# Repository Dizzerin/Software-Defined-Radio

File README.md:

# Software-Defined-Radio
This project is a quadrature sampling down converter software defined radio reciver for Engineering Electronics II at Walla Walla University.
My partners for this project were [Darius Felder](https://github.com/darius3241) and [Eric Walsh](https://github.com/Eric-Walsh).
For a quick look at the final results of our project jump to [results](#results).
For a quick setup guide jump to [Quisk setup](#quisk-setup).

## Design Objectives
Our professor, [Dr. Rob Frohne](https://github.com/frohro), gave us the following design objectives:
  1. Minimum discernible signal less than 1μV
  2. Good image rejection
  3. Low noise figure
  4. Inexpensive to build

  1. **Simple Design**: We wanted our design to be easy to understand and construct
  2. **Ease of Construction**: We wanted to build a simple radio that works
  3. **Low Cost**: Our budget for this project was $30
  
## Overview
The Software Defined Radio (SDR) receiver connects to an antenna and covers the filtering, mixing, and amplification of the desired signal. It then connects a sound card within a computer and software handles the demodulation of the signal into playable audio. The mixing is handled using an Arduino Nano running code provided to us by our Professor, [Dr. Rob Frohne](https://github.com/frohro), which interfaces with [Quisk](https://james.ahlstrom.name/quisk/), an SDR that controls the receiver through the Arduino. Using Quisk, the radio can be tuned to a certain frequency by adjusting the speed of the local oscillator used in the mixing process. Our budget on this project to keep with the low-cost aspect was about $30 including fabrication of the PCB and the required components. 

Note: Overview section by [Konrad McClure](https://github.com/KonradMcClure)

## Theory
The basics of the SDR Receiver are shown below in the block diagram, with the blue components being defined by software. An antenna picks up the radio signal and passes it through a bandpass filter. This filter will attenuate any signals outside our desired range of 6–16 MHz. This is then passed through a Tayloe Mixer, also known as the Tayloe Quadrature Product Detector. The Tayloe Mixer is a simple and efficient mixer that uses a 1:4 demultiplexer and operational amplifiers to generate the I and Q quadrature signals for demodulation. After the signal has been split into four bandbase signals, they are amplified and combined into the I and Q quadrature signals. Those signals go through a final Low-Pass filter that will attenuate signals above 100KHz in frequency, effectively smoothing the output signal. This signal is then sent via 3.5mm audio cable to the soundcard which demodulates the signal. Quisk can then read the input from the sound card and play it. Quisk also interfaces to the Arduino Nano to set the speed of the local oscillator for tuning into the desired frequency.

Note: This Theory Section is a slightly modified version of work originally written by [Konrad McClure](https://github.com/KonradMcClure)

## Design 
Here is a basic block diagram of our design:

## Schematic 

### List of components

### Voltage smoother 
This was added to smooth out 5V power supply from USB. This will help elimate supply noise.

### Voltage converter
This device converts the 5V logic of the arduino nano to the 3.3V logic of the Si5351a for both directions.

### Local Oscillator (Si5351a)
The local oscillator we used, SI5351-AB-GT clock generator was selected largely due to the fact that Dr. Frohne has used this chip with success.

### Mixer (tayloe)
The Tayloe Mixer is a mixer design as seen in [this paper](http://www.norcalqrp.org/files/Tayloe_mixer_x3a.pdf) by Dan Tayloe. We chose it due to its relatively simple and elegant design. It utilizes a [two-channel SN74CBT multiplexer](http://www.ti.com/lit/ds/symlink/sn74cbt3253.pdf?ts=1591655665924) and a pair of [INA821ID single gain resistor instrumentation amplifiers](http://www.ti.com/lit/ds/symlink/ina821.pdf?HQS=TI-null-null-mousermode-df-pf-null-wwe&DCM=yes&ref_url=https%3A%2F%2Fwww.mouser.com%2F&distId=26). To be more specific, Tayloe describes this as a "switching integrator," rather than a mixer, since a mixer normally produces both a sum and difference frequency of the RF and LO signals.

### Amplifiers
A Multiple feedback low pass filter and amplifier was used.

### Arduino Nano

## Simulation
Complete LTSpice model:

### Results of simulation

## Quisk setup
According to the [Quisk pip project description](https://pypi.org/project/quisk/), the [Quisk software](https://james.ahlstrom.name/quisk/) is "Software Defined Radio (SDR) transceiver software. You supply radio hardware that converts signals at the antenna to complex (I/Q) data at an intermediate frequency (IF). Data can come from a sound card, Ethernet or USB. Quisk then filters and demodulates the data and sends the audio to your speakers or headphones."  We used Quisk in our project for just this purpose.

To get Quisk up and running with our radio, simply:
1. Flash the [openradio_quisk.ino](openradio_quisk.ino) file to the arduino nano microcontroller.
2. Start Quisk and configure a new radio.  Point Quisk to the [quisk_conf_openradio.py](quisk_conf_openradio.py) file.  Alternatively you can simply copy the file to your home directory (~/.quisk_conf.py).

	Note: You may need to configure the following settings in this python file:
	* Sound card settings
	* Serial port settings
	
3. Restart Quisk tune to your desired frequency and listen away!

## Board build up plan 
See [board build up plan](https://github.com/darius3241/Software-Defined-Radio/wiki/Board-build-up-plan).

## Revisions and debugging 
See [revisions and debugging](https://github.com/darius3241/Software-Defined-Radio/wiki/Debugging-and-Revisions).

## Complete Design 
Photo of our complete board:

## Results
In the end, we had about 1μV of sensitivity and between 10 and 30 dB of image rejection. (Darius’
radio had about 10dB of rejection while mine had about 30dB of image rejection). Though our radios
are working, they have less sensitivity than desired and when we examine the waterfall spectral display
on Quisk there are some distinct lines. We believe these are from signals on the USB input, so it may be
worthwhile to investigate isolating this further in future revisions.

Credit to: Dr. Frohne for his extensive help with the debugging process.

## Future Revision Recomendations
Other recommendations for future revisions include using continuous rows of pin headers for test
points instead of single pin headers to ease soldering, include better ground test points (perhaps two
pads to solder a wire between which ground clips can be clipped onto), moving plastic components
further from surface mount chips which may need to be de-soldered, and including jumpers to allow the
op amps to be powered from an alternate power source separate from the 5V circuit so additional
power can be provided if desired without damaging other components.

## External tools used:
[Multiple Feedback Low-Pass Filter Design Tool](http://sim.okawa-denshi.jp/en/OPtazyuLowkeisan.htm)

[Third Order Butterworth Bandpass Filter Design Tool](https://rf-tools.com/lc-filter/)

## Credits
[Darius Felder](https://github.com/darius3241) - project partner primarily responsible for testing, simulations, and documentation

[Eric Walsh](https://github.com/Eric-Walsh) - project partner primarily responsible for testing and LTSpice simulations

[Dr. Frohne](https://github.com/frohro) - class professor

[Konrad McClure](https://github.com/KonradMcClure) - previous project pioneer

[Caleb Froelich](https://github.com/froeca) - previous project pioneer

[Jordyn Watkins](https://github.com/greenjacketgirl) - previous project pioneer

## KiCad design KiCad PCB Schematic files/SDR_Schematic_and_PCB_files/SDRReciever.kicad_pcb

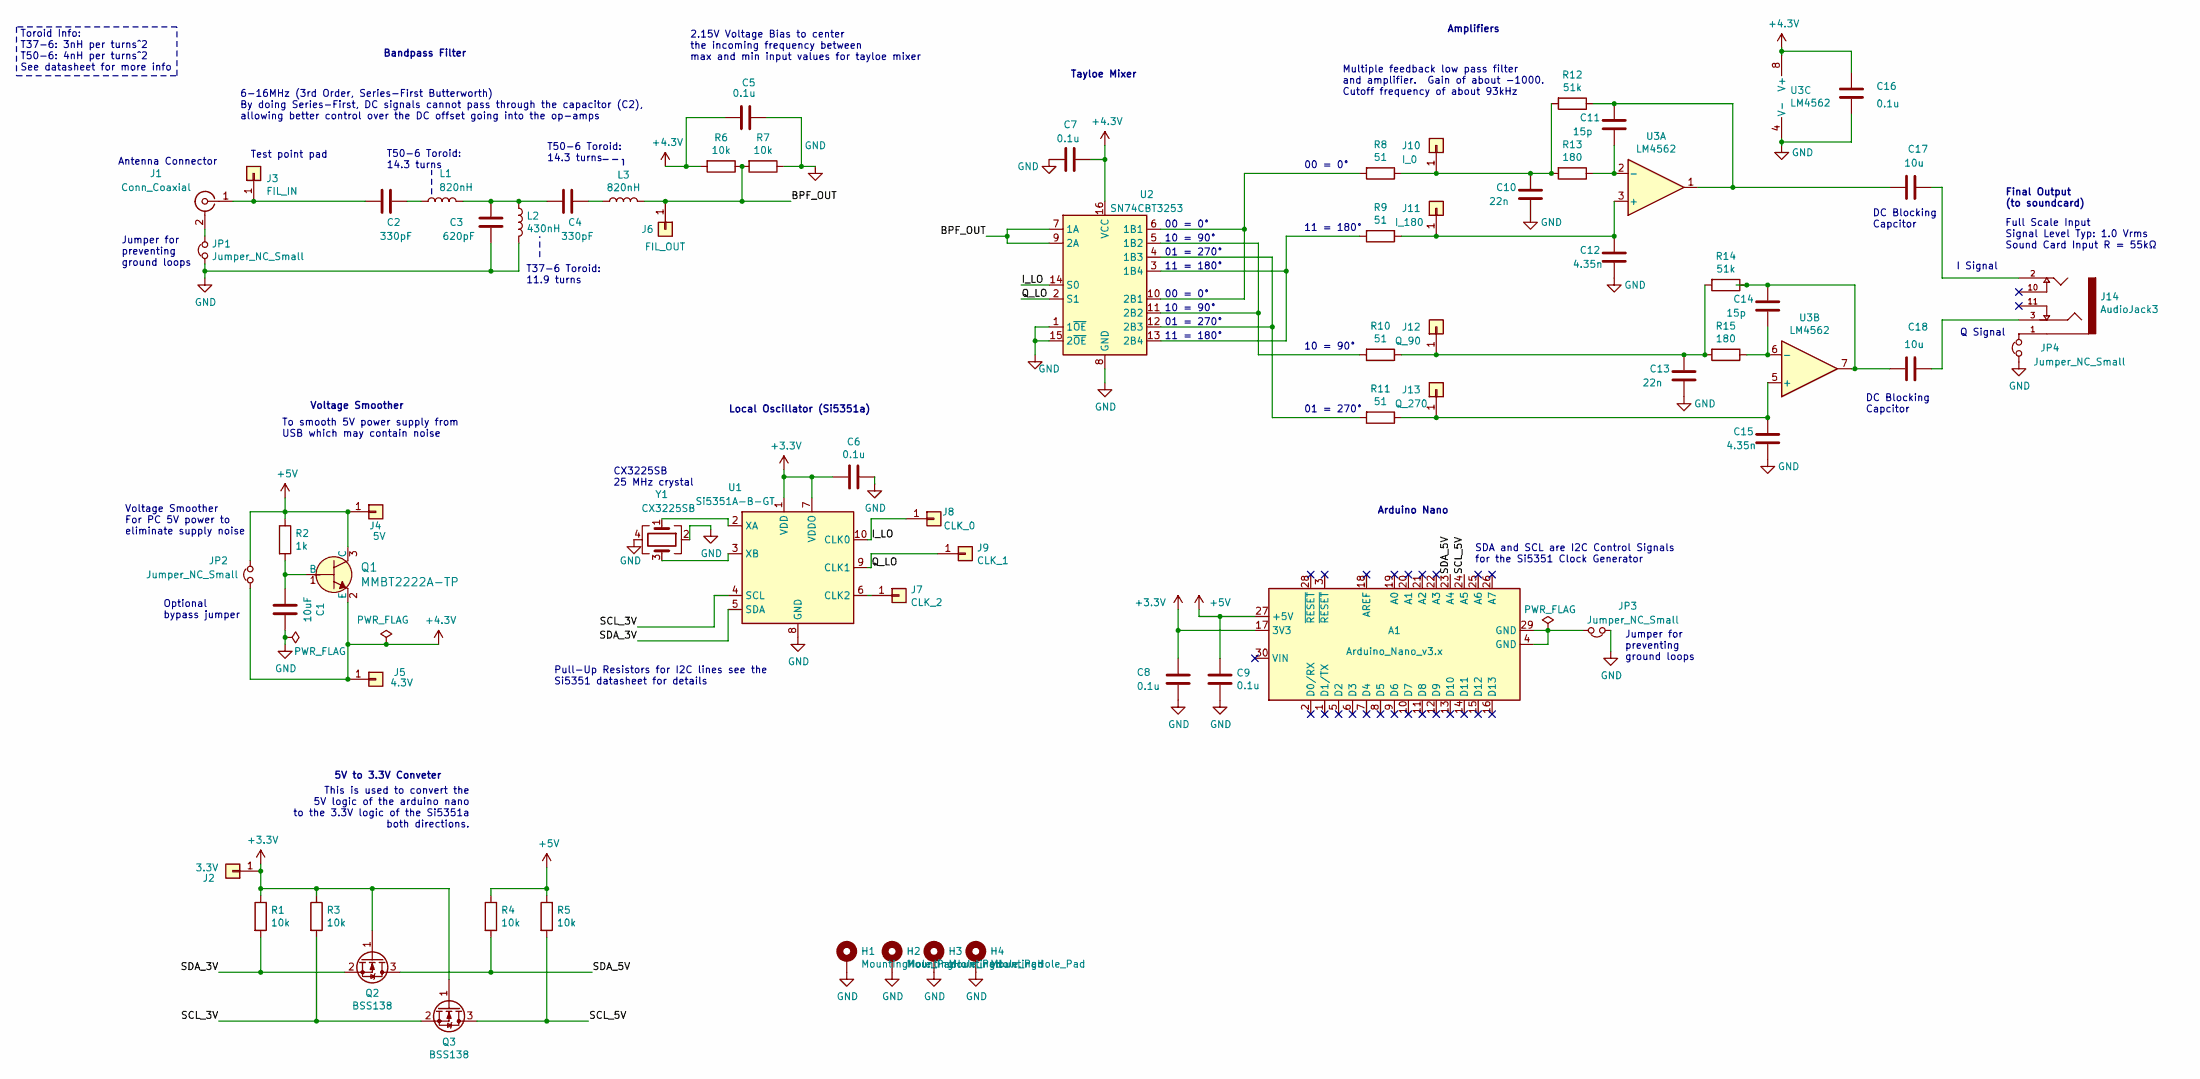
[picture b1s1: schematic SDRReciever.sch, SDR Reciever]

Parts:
A1: Arduino_Nano_v3.x; Arduino_Nano
C1: 10uF; C_0805_2012Metric
C2, C4: 330pF; C_0805_2012Metric
C3: 620pF; C_0805_2012Metric
C5, C6, C7, C8, C9, C16: 0.1u; C_0805_2012Metric
C10, C13: 22n; C_0805_2012Metric
C11, C14: 15p; C_0805_2012Metric
C12, C15: 4.35n; C_0805_2012Metric
C17, C18: 10u; C_0805_2012Metric
H1, H2, H3, H4: MountingHole_Pad; MountingHole_2.2mm_M2_Pad
J1: Conn_Coaxial; BNC_Amphenol_B6252HB-NPP3G-50_Horizontal
J2: 3.3V; PinHeader_1x01_P2.54mm_Vertical
J3: FIL_IN; PinHeader_1x01_P2.54mm_Vertical
J4: 5V; PinHeader_1x01_P2.54mm_Vertical
J5: 4.3V; PinHeader_1x01_P2.54mm_Vertical
J6: FIL_OUT; PinHeader_1x01_P2.54mm_Vertical
J7: CLK_2; PinHeader_1x01_P2.54mm_Vertical
J8: CLK_0; PinHeader_1x01_P2.54mm_Vertical
J9: CLK_1; PinHeader_1x01_P2.54mm_Vertical
J10: I_0; PinHeader_1x01_P2.54mm_Vertical
J11: I_180; PinHeader_1x01_P2.54mm_Vertical
J12: Q_90; PinHeader_1x01_P2.54mm_Vertical
J13: Q_270; PinHeader_1x01_P2.54mm_Vertical
J14: AudioJack3; 35RAPC4BHN2
JP1, JP2, JP3, JP4: Jumper_NC_Small; PinHeader_1x02_P2.54mm_Vertical
L1, L3: 820nH; L_Toroid_Vertical_L13.0mm_W6.5mm_P5.60mm
L2: 430nH; L_Toroid_Vertical_L10.0mm_W5.0mm_P5.08mm
Q1: MMBT2222A-TP; SOT-23-3; MPN MMBT2222A-TP; Digi-Key_PN MMBT2222ATPMSCT-ND
Q2, Q3: BSS138; SOT-23
R1, R3, R4, R5, R6, R7: 10k; R_0805_2012Metric
R2: 1k; R_0805_2012Metric
R8, R9, R10, R11: 51; R_0805_2012Metric
R12, R14: 51k; R_0805_2012Metric
R13, R15: 180; R_0805_2012Metric
U1: Si5351A-B-GT; MSOP-10_3x3mm_P0.5mm
U2: SN74CBT3253; SOIC-16_3.9x9.9mm_P1.27mm
U3: LM4562; SOIC-8_3.9x4.9mm_P1.27mm
Y1: CX3225SB; Crystal_SMD_Abracon_ABM8G-4Pin_3.2x2.5mm

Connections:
+3V3: A1.17 (3V3), C6.2, C8.1, J2.1, Q2.1 (G), Q3.1 (G), R1.1, R3.1, U1.1 (VDD), U1.7 (VDDO)
+4.3V: C5.1, C7.1, C16.1, J5.1, JP2.1, Q1.2 (E), R6.2, U2.16 (VCC), U3.8 (V+)
+5V: A1.27 (+5V), C9.1, J4.1, JP2.2, Q1.3 (C), R2.1, R4.1, R5.1
/BPF_OUT: J6.1, L3.2, R6.1, R7.2, U2.7 (1A), U2.9 (2A)
/I_LO: J8.1, U1.10 (CLK0), U2.14 (S0)
/Q_LO: J9.1, U1.9 (CLK1), U2.2 (S1)
/SCL_3V: Q3.2 (S), R3.2, U1.4 (SCL)
/SCL_5V: A1.24 (A5), Q3.3 (D), R5.2
/SDA_3V: Q2.2 (S), R1.2, U1.5 (SDA)
/SDA_5V: A1.23 (A4), Q2.3 (D), R4.2
GND: C1.1, C3.1, C5.2, C6.1, C7.2, C8.2, C9.2, C10.2, C12.2, C13.2, C15.2, C16.2, H1.1, H2.1, H3.1, H4.1, JP1.1, JP3.1, JP4.1, L2.2, R7.1, U1.8 (GND), U2.1 (1~OE), U2.8 (GND), U2.15 (2~OE), U3.4 (V-), Y1.2, Y1.4
unnamed: A1.4 (GND), A1.29 (GND), JP3.2
unnamed: C1.2, Q1.1 (B), R2.2
unnamed: C2.1, J1.1 (In), J3.1
unnamed: C2.2, L1.1
unnamed: C3.2, C4.1, L1.2, L2.1
unnamed: C4.2, L3.1
unnamed 17: C10.1, J10.1, R8.1, R12.2, R13.2; also elsewhere on the board
unnamed: C11.1, C17.2, R12.1, U3.1
unnamed: C11.2, R13.1, U3.2 (-)
unnamed 20: C12.1, J11.1, R9.1, U3.3 (+); also elsewhere on the board
unnamed 21: C13.1, J12.1, R10.1, R14.2, R15.2; also elsewhere on the board
unnamed: C14.1, C18.2, R14.1, U3.7
unnamed: C14.2, R15.1, U3.6 (-)
unnamed 24: C15.1, J13.1, R11.1, U3.5 (+); also elsewhere on the board
unnamed: C17.1, J14.2
unnamed: C18.1, J14.3
unnamed: J1.2 (Ext), JP1.2
unnamed: J7.1, U1.6 (CLK2)
unnamed: J14.1, JP4.2
unnamed: R8.2, U2.6 (1B1), U2.10 (2B1)
unnamed: R9.2, U2.3 (1B4), U2.13 (2B4)
unnamed: R10.2, U2.5 (1B2), U2.11 (2B2)
unnamed: R11.2, U2.4 (1B3), U2.12 (2B3)
unnamed: U1.2 (XA), Y1.1
unnamed: U1.3 (XB), Y1.3

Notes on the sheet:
2.15V Voltage Bias to center the incoming frequency between max and min input values for tayloe mixer
Full Scale Input Signal Level Typ: 1.0 Vrms Sound Card Input R = 55kΩ
Multiple feedback low pass filter and amplifier. Gain of about -1000. Cutoff frequency of about 93kHz
Voltage Smoother For PC 5V power to eliminate supply noise
T50-6 Toroid: 14.3 turns
T37-6 Toroid: 11.9 turns
Pull-Up Resistors for I2C lines see the Si5351 datasheet for details
SDA and SCL are I2C Control Signals for the Si5351 Clock Generator
Jumper for preventing ground loops
CX3225SB 25 MHz crystal
00 = 0°
11 = 180°
10 = 90°
01 = 270°
6-16MHz (3rd Order, Series-First Butterworth) By doing Series-First, DC signals cannot pass through the capacitor (C2), allowing better control over the DC offset going into the op-amps
Toroid Info: T37-6: 3nH per turns^2 T50-6: 4nH per turns^2 See datasheet for more info
Antenna Connector
Test point pad
Bandpass Filter
Local Oscillator (Si5351a)
Arduino Nano
Tayloe Mixer
Final Output (to soundcard)
5V to 3.3V Conveter
This is used to convert the 5V logic of the arduino nano to the 3.3V logic of the Si5351a both directions.
I Signal
Amplifiers
Q Signal
Voltage Smoother
To smooth 5V power supply from USB which may contain noise
Optional bypass jumper
DC Blocking Capcitor

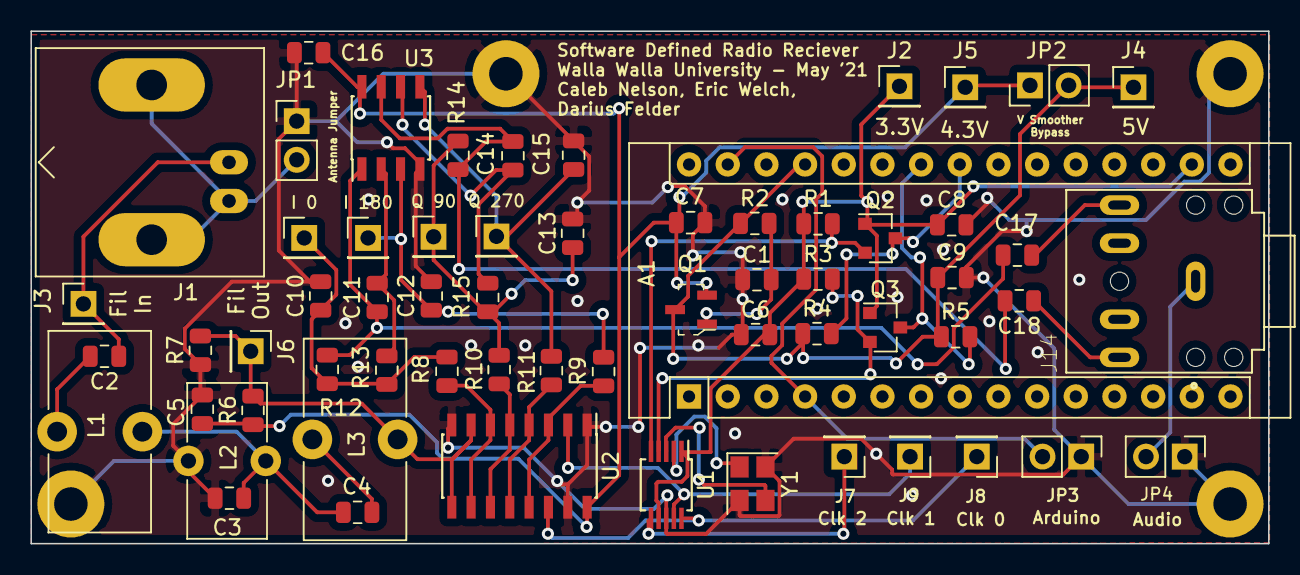
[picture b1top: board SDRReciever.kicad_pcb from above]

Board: 2 copper layers, 81.3 x 33.7 mm, 66 parts (0 on the bottom side), 36 nets.

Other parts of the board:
I 0: I_0; PinHeader_1x01_P2.54mm_Vertical
I 180: I_180; PinHeader_1x01_P2.54mm_Vertical
Q 90: Q_90; PinHeader_1x01_P2.54mm_Vertical
Q 270: Q_270; PinHeader_1x01_P2.54mm_Vertical

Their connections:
unnamed 17: I 0.1; also elsewhere on the board
unnamed 20: I 180.1; also elsewhere on the board
unnamed 21: Q 90.1; also elsewhere on the board
unnamed 24: Q 270.1; also elsewhere on the board

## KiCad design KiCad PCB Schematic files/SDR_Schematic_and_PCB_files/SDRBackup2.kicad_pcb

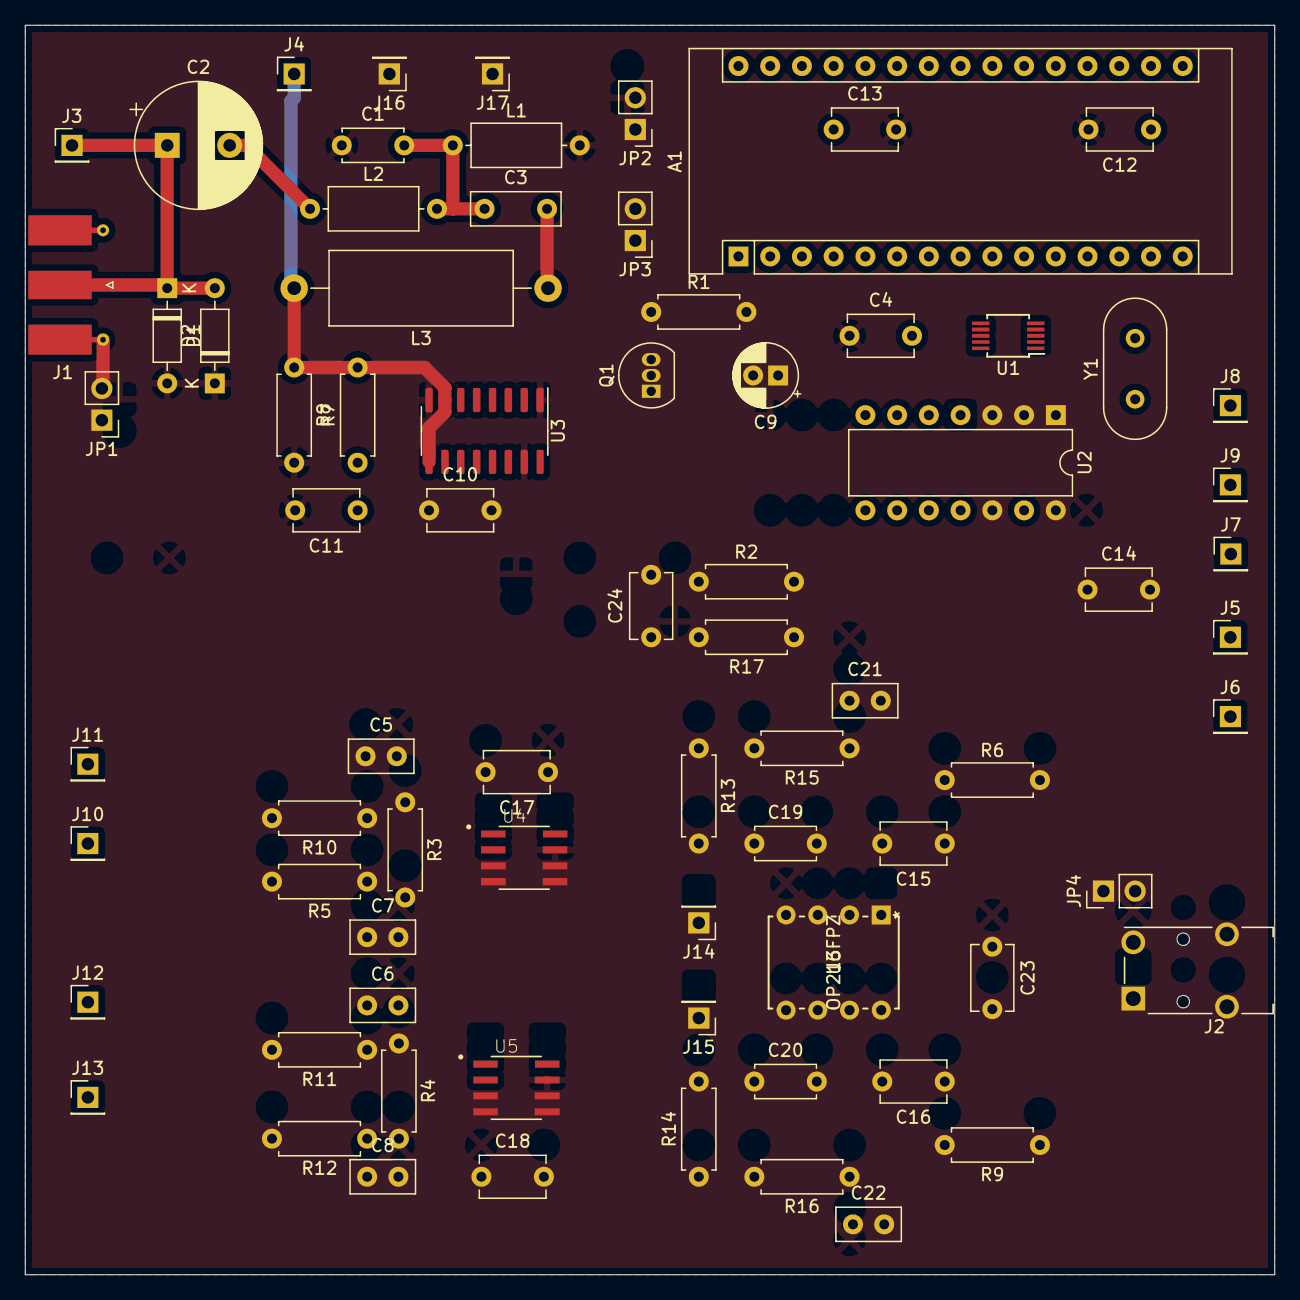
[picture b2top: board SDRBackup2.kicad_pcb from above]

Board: 2 copper layers, 100.0 x 100.0 mm, 76 parts (0 on the bottom side), 48 nets.

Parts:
A1: Arduino_Nano_v3.x; Arduino_Nano
C1: 680p; C_Disc_D4.7mm_W2.5mm_P5.00mm
C2: 910u; CP_Radial_D10.0mm_P5.00mm
C3: 150p; C_Disc_D7.0mm_W2.5mm_P5.00mm
C4, C10, C11, C12, C13, C14, C15, C16, C17, C18, C23, C24: 0.1u; C_Disc_D5.1mm_W3.2mm_P5.00mm
C5, C6, C7, C8, C21, C22: 100p; C_Disc_D5.0mm_W2.5mm_P2.50mm
C9: 10uF; CP_Radial_D5.0mm_P2.00mm
C19, C20: 220p; C_Disc_D4.7mm_W2.5mm_P5.00mm
D1, D2: 1N914; D_DO-35_SOD27_P7.62mm_Horizontal
J1: Conn_Coaxial; SMA_Molex_73251-1153_EdgeMount_Horizontal
J2: AudioJack3; Jack_3.5mm_Switronic_ST-005-G_horizontal
J3: FIL_I; PinHeader_1x01_P2.54mm_Vertical
J4: FIL_O; PinHeader_1x01_P2.54mm_Vertical
J5: CLK_2; PinHeader_1x01_P2.54mm_Vertical
J6: CLK_3; PinHeader_1x01_P2.54mm_Vertical
J7: CLK_1; PinHeader_1x01_P2.54mm_Vertical
J8: I_LO; PinHeader_1x01_P2.54mm_Vertical
J9: Q_LO; PinHeader_1x01_P2.54mm_Vertical
J10: I_0; PinHeader_1x01_P2.54mm_Vertical
J11: I_180; PinHeader_1x01_P2.54mm_Vertical
J12: Q_90; PinHeader_1x01_P2.54mm_Vertical
J13: Q_270; PinHeader_1x01_P2.54mm_Vertical
J14: I_OUT; PinHeader_1x01_P2.54mm_Vertical
J15: Q_OUT; PinHeader_1x01_P2.54mm_Vertical
J16: 5V; PinHeader_1x01_P2.54mm_Vertical
J17: 4.3V; PinHeader_1x01_P2.54mm_Vertical
JP1, JP2, JP3, JP4: Jumper_NC_Small; PinHeader_1x02_P2.54mm_Vertical
L1, L2: 1u; L_Axial_L7.0mm_D3.3mm_P10.16mm_Horizontal_Fastron_MICC
L3: 3.6u; L_Axial_L14.5mm_D5.8mm_P20.32mm_Horizontal_Fastron_HBCC
Q1: PN2222A; TO-92_Inline
R1: 1k; R_Axial_DIN0207_L6.3mm_D2.5mm_P7.62mm_Horizontal
R2, R7, R8, R17: 10k; R_Axial_DIN0207_L6.3mm_D2.5mm_P7.62mm_Horizontal
R3, R4: 33; R_Axial_DIN0207_L6.3mm_D2.5mm_P7.62mm_Horizontal
R5, R10, R11, R12: 50; R_Axial_DIN0207_L6.3mm_D2.5mm_P7.62mm_Horizontal
R6, R9: 100; R_Axial_DIN0207_L6.3mm_D2.5mm_P7.62mm_Horizontal
R13, R14: 8.2k; R_Axial_DIN0207_L6.3mm_D2.5mm_P7.62mm_Horizontal
R15, R16: 15k; R_Axial_DIN0207_L6.3mm_D2.5mm_P7.62mm_Horizontal
U1: Si5351A-B-GT; MSOP-10_3x3mm_P0.5mm
U2: 74AC74; DIP-14_W7.62mm
U3: SN74CBT3253; SOIC-16_3.9x9.9mm_P1.27mm
U4, U5: INA821ID; SOIC127P600X175-8N
U6: OP213FPZ
Y1: Crystal; Crystal_HC49-U_Vertical

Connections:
+3V3: A1.17, C4.2, C12.1, C14.1, U1.1, U1.7, U2.1, U2.4, U2.10, U2.13, U2.14
+4.3V: C10.1, C11.1, C17.2, C18.2, C23.2, C24.2, J17.1, JP3.1, Q1.1, R2.1, R7.1, U3.16, U4.8, U5.8, U6.8
+5V: A1.27, C13.1, J16.1, JP3.2, Q1.3, R1.1
/FIL_OUT: J4.1, L3.2, R7.2, R8.1, U3.7, U3.9
/I_LO: J8.1, U2.6, U3.14
/Q_LO: J9.1, U2.2, U2.8, U3.2
/SCL: A1.24, U1.4
/SDA: A1.23, U1.5
GND: C1.1, C4.1, C5.2, C6.2, C7.2, C8.2, C9.1, C10.2, C11.2, C12.2, C13.2, C14.2, C17.1, C18.1, C21.2, C22.2, C23.1, C24.1, D1.2, D2.1, JP1.1, JP2.1, JP4.1, L1.2, R8.2, R17.2, U1.8, U2.7, U3.1, U3.8, U3.15, U4.5, U5.5, U6.4
GNDA: R2.2, R17.1, U4.6, U5.6
unnamed: A1.4, A1.29, JP2.2
unnamed: C1.2, C3.1, L1.1, L2.2
unnamed: C2.1, D1.1, D2.2, J1.1, J3.1
unnamed: C2.2, L2.1
unnamed: C3.2, L3.1
unnamed: C5.1, J11.1, R10.1, U4.1
unnamed: C6.1, J13.1, R12.1, U5.1
unnamed: C7.1, J10.1, R5.1, U4.4
unnamed: C8.1, J12.1, R11.1, U5.4
unnamed: C9.2, Q1.2, R1.2
unnamed: C15.1, R6.1
unnamed: C15.2, C19.2, U6.1, U6.2
unnamed: C16.1, R9.2
unnamed: C16.2, C20.2, U6.6, U6.7
unnamed: C19.1, R13.1, R15.2
unnamed: C20.1, R14.1, R16.2
unnamed: C21.1, R15.1, U6.3
unnamed: C22.1, R16.1, U6.5
unnamed: J1.2, JP1.2
unnamed: J2.R, R9.1
unnamed: J2.S, JP4.2
unnamed: J2.T, R6.2
unnamed: J5.1, U1.9
unnamed: J6.1, U1.6
unnamed: J7.1, U1.10, U2.3, U2.11
unnamed: J14.1, R13.2, U4.7
unnamed: J15.1, R14.2, U5.7
unnamed: R3.1, U4.2
unnamed: R3.2, U4.3
unnamed: R4.1, U5.2
unnamed: R4.2, U5.3
unnamed: R5.2, U3.6, U3.10
unnamed: R10.2, U3.3, U3.13
unnamed: R11.2, U3.5, U3.11
unnamed: R12.2, U3.4, U3.12
unnamed: U1.2, Y1.1
unnamed: U1.3, Y1.2
unnamed: U2.5, U2.12

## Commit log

2021-04-12 Created some initial folders
2021-04-14 Initial KiCad Schematic and PCB files
2021-04-14 Removed unnecessary files and components
2021-04-17 Updated values for bandpass filter in KiCad schematic Now a 3-rd order, series first, butterworth filter passing 6-16Mhz Also added some additional comments to KiCad schematic
2021-04-19 Added .gitignore
2021-04-19 adding LTSpice files
2021-04-19 Updated schematic, added voltage converter and comments
2021-04-19 BPF Vaules Updated
2021-04-26 adding a spice file rq
2021-04-27 Updated KiCad Schematic 1. Exchanged instrumentation amplifiers and following op amp low pass filters for a single set of low noise op amps with multiple feedback and two poles of attenuation. 2. Rem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
2021-04-27 Removed diodes, added test point
2021-04-27 Removed old KiCad version files, kept the latest and removed *02 appending
2021-04-29 Revision 0.3 of schematic Added bypass cap Added DC blocking caps Removed redudant resitors Added custom footprints Updated BNC connector footprint Updated audo jack footprint, schematic symbol, conn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
2021-04-29 Added PDFs of Schematic
2021-04-29 Added first transient simulation
2021-04-29 Exchanged transistor for surface mount transistor Updated resistor values to standard values
2021-04-29 Added reciever simulation
2021-04-30 Initial PCB part layout complete Trace not routed yet
2021-04-30 Revised PCB part placement
2021-04-30 added simulation test files and made some changes to the main simulation file
2021-04-30 Revised placement of PCB parts
2021-04-30 Initial PCB tracing complete
2021-04-30 Added more vias to improve ground plane on PCB
2021-05-01 Revision 1 complete First complete PCB design.
2021-05-01 Updated simulation test (got rid of the jumper cable from the RF source to ground)
2021-05-01 PCB revision 1 complete. Added 3D model and updated silk screen.
2021-05-03 Got the Mixer and amp model to output a graph
2021-05-03 Mixer and amp with 100µs delay
2021-05-05 Added Gerbers, Drill Files, and Interactive BOM (Bill of Materials)
2021-05-05 Updated schematic pdfs to latest version (revision 1)
2021-05-22 Added basic test files for si5351a clock chip
2021-06-02 Added Quisk Software files, updated si5351a oscillator test file. Need to look into clock 1 and clock 2 working with quisk.
2021-06-11 Updated Readme Documentation
2021-06-11 More updates to readme. Fixed bug with Quisk Code.

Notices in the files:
parts and their libraries:
Copyright 2016 Accelerated Designs. All rights reserved.
